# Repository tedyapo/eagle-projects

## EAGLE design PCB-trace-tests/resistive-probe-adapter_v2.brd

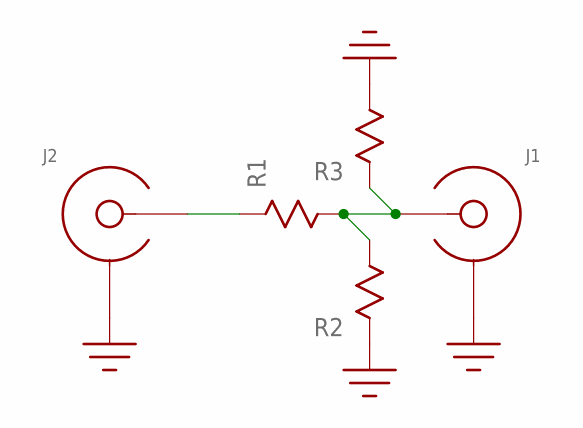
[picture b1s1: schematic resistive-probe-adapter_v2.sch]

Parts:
J1, J2: SMA-EDGE-LAUNCH4020_TAPER; SMA_EDGE_LAUNCH_2L_4020_TAPER
R1, R2, R3: R0603

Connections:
GND: J1.BOTTOM_GND (SHIELD), J1.GND@1 (SHIELD), J1.GND@2 (SHIELD), J1.GND@3 (SHIELD), J1.GND@4 (SHIELD), J1.GND@5 (SHIELD), J1.GND@6 (SHIELD), J1.GND@7 (SHIELD), J1.GND@8 (SHIELD), J1.GND@14 (SHIELD), J1.GND@15 (SHIELD), J1.GND@16 (SHIELD), J1.GND@17 (SHIELD), J1.GND_PAD1 (SHIELD), J1.GND_PAD2 (SHIELD), J1.P$1 (SHIELD), J1.P$2 (SHIELD), J2.BOTTOM_GND (SHIELD), J2.GND@1 (SHIELD), J2.GND@2 (SHIELD), J2.GND@3 (SHIELD), J2.GND@4 (SHIELD), J2.GND@5 (SHIELD), J2.GND@6 (SHIELD), J2.GND@7 (SHIELD), J2.GND@8 (SHIELD), J2.GND@14 (SHIELD), J2.GND@15 (SHIELD), J2.GND@16 (SHIELD), J2.GND@17 (SHIELD), J2.GND_PAD1 (SHIELD), J2.GND_PAD2 (SHIELD), J2.P$1 (SHIELD), J2.P$2 (SHIELD), R2.P$1, R3.P$2
unnamed: J2.CENTER@1 (CENTER), R1.P$1
unnamed: J1.CENTER@1 (CENTER), R1.P$2, R2.P$2, R3.P$1

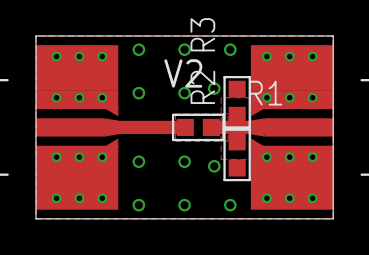
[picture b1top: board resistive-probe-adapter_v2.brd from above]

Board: 2 copper layers, 16.5 x 10.2 mm, 5 parts (0 on the bottom side), 3 nets.

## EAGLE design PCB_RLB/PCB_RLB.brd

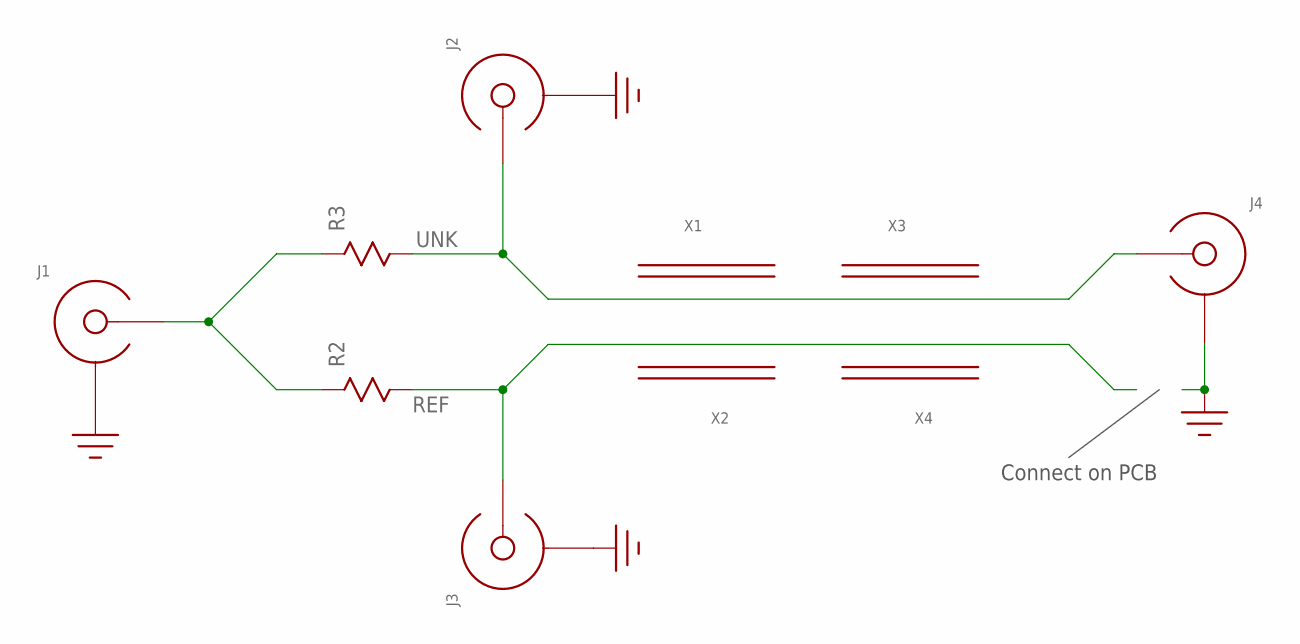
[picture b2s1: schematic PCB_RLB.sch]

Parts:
J1, J2, J3, J4: EDGE_LAUNCH_JACK; EDGE_LAUNCH_RF_CON
R2, R3: R0603
X1, X2, X3, X4: FERRITE_PLATE; FERRITE-MP0350

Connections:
GND: J1.GND@1 (SHIELD), J1.GND@2 (SHIELD), J1.GND@3 (SHIELD), J1.GND@4 (SHIELD), J1.GND@5 (SHIELD), J1.GND@6 (SHIELD), J1.GND@7 (SHIELD), J1.GND@8 (SHIELD), J1.GND@9 (SHIELD), J1.GND@10 (SHIELD), J1.GND@11 (SHIELD), J1.GND@12 (SHIELD), J1.SHIELD@1 (SHIELD), J1.SHIELD@2 (SHIELD), J2.GND@1 (SHIELD), J2.GND@2 (SHIELD), J2.GND@3 (SHIELD), J2.GND@4 (SHIELD), J2.GND@5 (SHIELD), J2.GND@6 (SHIELD), J2.GND@7 (SHIELD), J2.GND@8 (SHIELD), J2.GND@9 (SHIELD), J2.GND@10 (SHIELD), J2.GND@11 (SHIELD), J2.GND@12 (SHIELD), J2.SHIELD@1 (SHIELD), J2.SHIELD@2 (SHIELD), J3.GND@1 (SHIELD), J3.GND@2 (SHIELD), J3.GND@3 (SHIELD), J3.GND@4 (SHIELD), J3.GND@5 (SHIELD), J3.GND@6 (SHIELD), J3.GND@7 (SHIELD), J3.GND@8 (SHIELD), J3.GND@9 (SHIELD), J3.GND@10 (SHIELD), J3.GND@11 (SHIELD), J3.GND@12 (SHIELD), J3.SHIELD@1 (SHIELD), J3.SHIELD@2 (SHIELD), J4.GND@1 (SHIELD), J4.GND@2 (SHIELD), J4.GND@3 (SHIELD), J4.GND@4 (SHIELD), J4.GND@5 (SHIELD), J4.GND@6 (SHIELD), J4.GND@7 (SHIELD), J4.GND@8 (SHIELD), J4.GND@9 (SHIELD), J4.GND@10 (SHIELD), J4.GND@11 (SHIELD), J4.GND@12 (SHIELD), J4.SHIELD@1 (SHIELD), J4.SHIELD@2 (SHIELD)
unnamed: J1.CENTER, R2.P$1, R3.P$1
REF: J3.CENTER, R2.P$2
UNK: J2.CENTER, J4.CENTER, R3.P$2

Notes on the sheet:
Connect on PCB

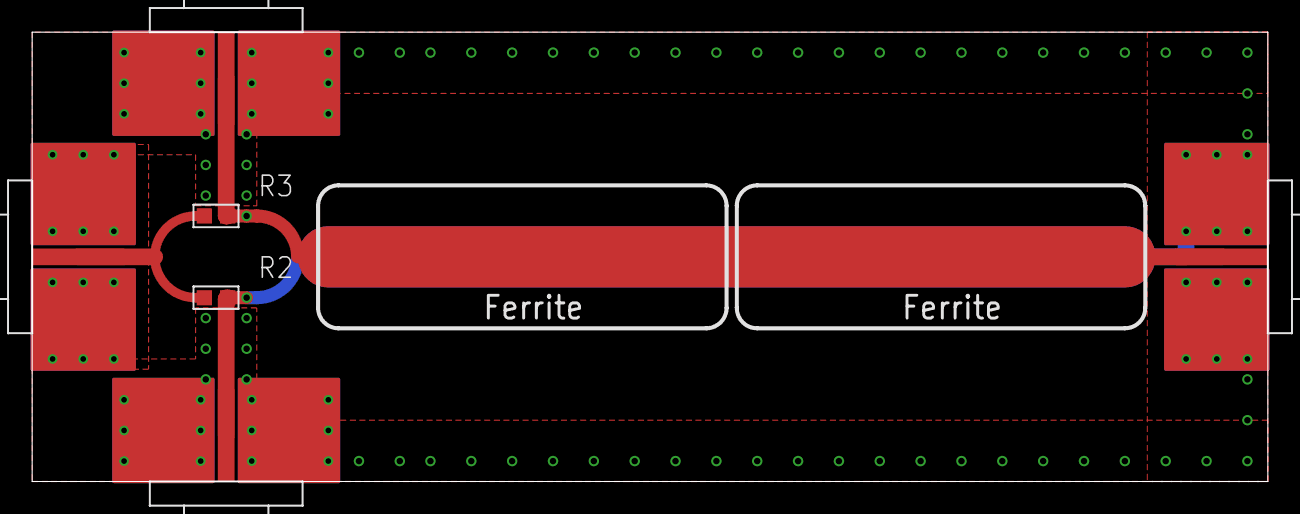
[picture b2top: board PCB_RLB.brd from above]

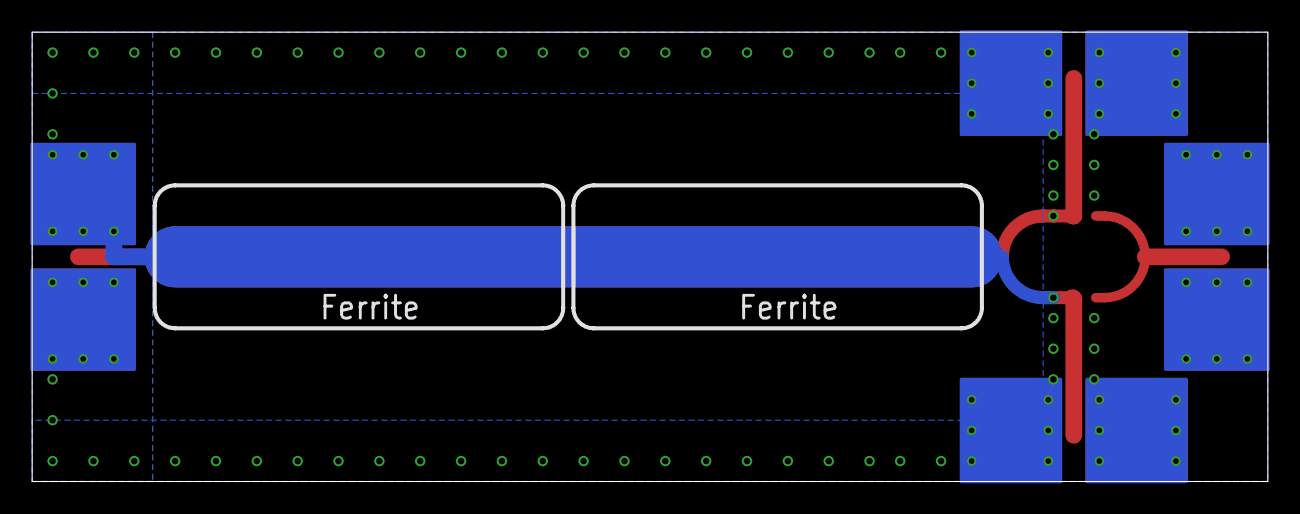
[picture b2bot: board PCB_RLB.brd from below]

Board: 2 copper layers, 76.8 x 27.9 mm, 10 parts (2 on the bottom side), 4 nets.

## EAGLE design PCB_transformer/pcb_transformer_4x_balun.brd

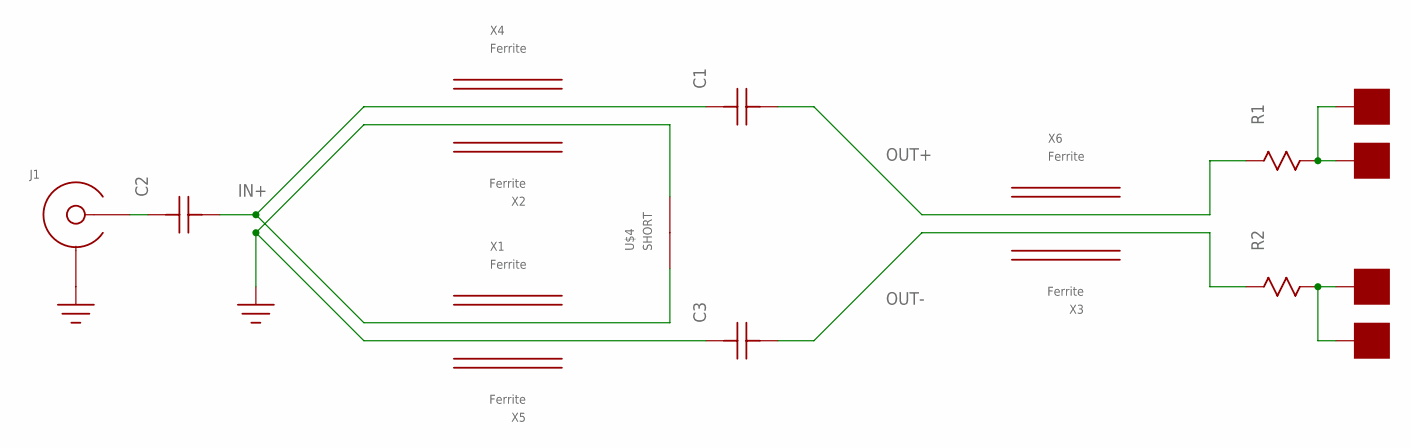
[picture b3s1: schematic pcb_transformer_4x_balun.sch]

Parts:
C1, C2, C3: C0603
J1: EDGE_LAUNCH_JACK; EDGE_LAUNCH_RF_CON
R1, R2: R0603
U$2, U$5, U$6, U$7: PAD50MIL; PAD_50MIL
U$4: SHORT; SHORT_57MIL
X1, X2, X3, X4, X5, X6: Ferrite; FERRITE-MP0350

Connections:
GND: C3.P$2, J1.GND@1 (SHIELD), J1.GND@2 (SHIELD), J1.GND@3 (SHIELD), J1.GND@4 (SHIELD), J1.GND@5 (SHIELD), J1.GND@6 (SHIELD), J1.GND@7 (SHIELD), J1.GND@8 (SHIELD), J1.GND@9 (SHIELD), J1.GND@10 (SHIELD), J1.GND@11 (SHIELD), J1.GND@12 (SHIELD), J1.SHIELD@1 (SHIELD), J1.SHIELD@2 (SHIELD), U$4.P$2
IN+: C1.P$2, C2.P$1, U$4.P$1
unnamed: C2.P$2, J1.CENTER
unnamed: R1.P$2, U$2.P$1, U$6.P$1
unnamed: R2.P$2, U$5.P$1, U$7.P$1
OUT+: C1.P$1, R1.P$1
OUT-: C3.P$1, R2.P$1

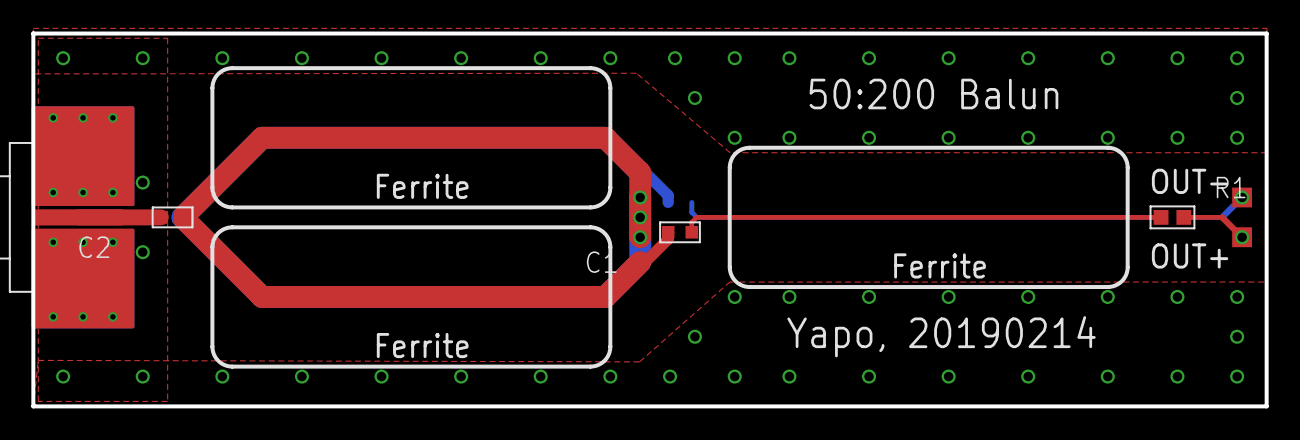
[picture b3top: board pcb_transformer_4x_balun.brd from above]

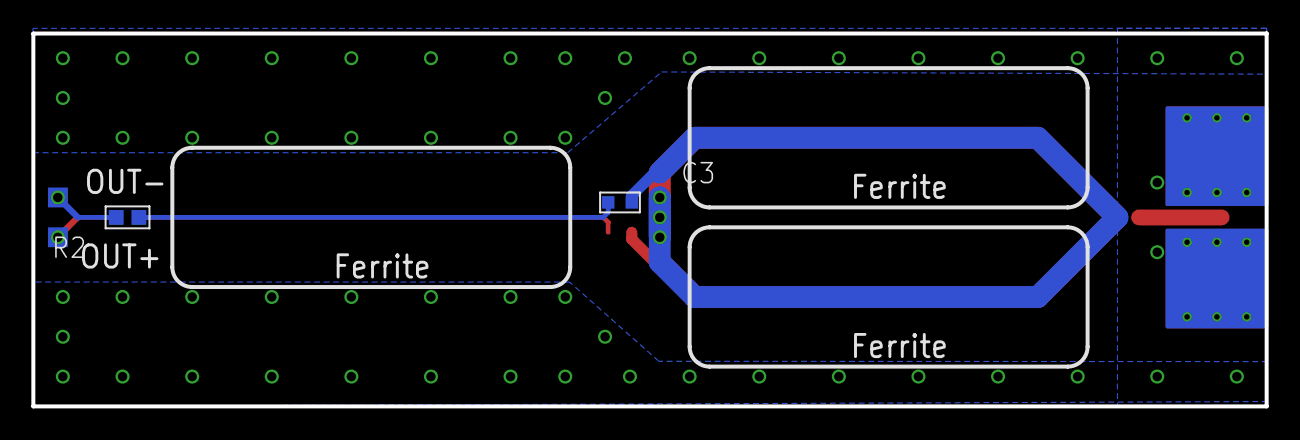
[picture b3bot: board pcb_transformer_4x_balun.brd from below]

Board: 2 copper layers, 78.7 x 23.8 mm, 17 parts (7 on the bottom side), 7 nets.

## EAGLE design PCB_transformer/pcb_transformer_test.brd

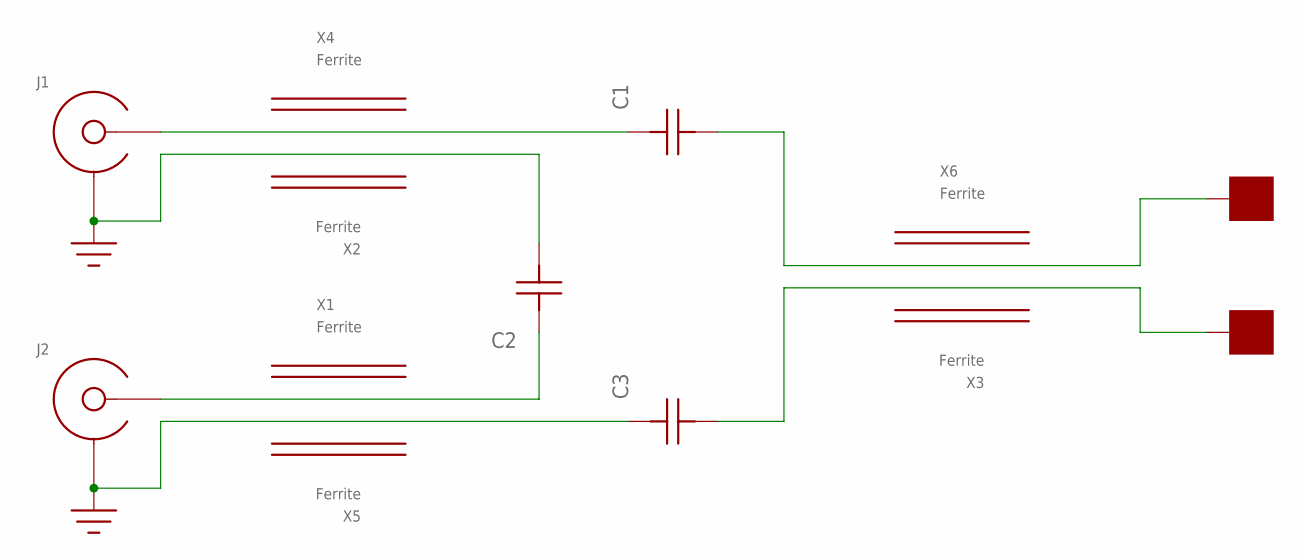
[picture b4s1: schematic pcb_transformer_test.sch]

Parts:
C1, C2, C3: C0603
J1, J2: EDGE_LAUNCH_JACK; EDGE_LAUNCH_RF_CON
U$2, U$5: PAD50MIL; PAD_50MIL
X1, X2, X3, X4, X5, X6: Ferrite; FERRITE-MP0350

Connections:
GND: C2.P$1, C3.P$2, J1.GND@1 (SHIELD), J1.GND@2 (SHIELD), J1.GND@3 (SHIELD), J1.GND@4 (SHIELD), J1.GND@5 (SHIELD), J1.GND@6 (SHIELD), J1.GND@7 (SHIELD), J1.GND@8 (SHIELD), J1.GND@9 (SHIELD), J1.GND@10 (SHIELD), J1.GND@11 (SHIELD), J1.GND@12 (SHIELD), J1.SHIELD@1 (SHIELD), J1.SHIELD@2 (SHIELD), J2.GND@1 (SHIELD), J2.GND@2 (SHIELD), J2.GND@3 (SHIELD), J2.GND@4 (SHIELD), J2.GND@5 (SHIELD), J2.GND@6 (SHIELD), J2.GND@7 (SHIELD), J2.GND@8 (SHIELD), J2.GND@9 (SHIELD), J2.GND@10 (SHIELD), J2.GND@11 (SHIELD), J2.GND@12 (SHIELD), J2.SHIELD@1 (SHIELD), J2.SHIELD@2 (SHIELD)
unnamed: C1.P$2, J1.CENTER
unnamed: C2.P$2, J2.CENTER
unnamed: C1.P$1, U$2.P$1
unnamed: C3.P$1, U$5.P$1

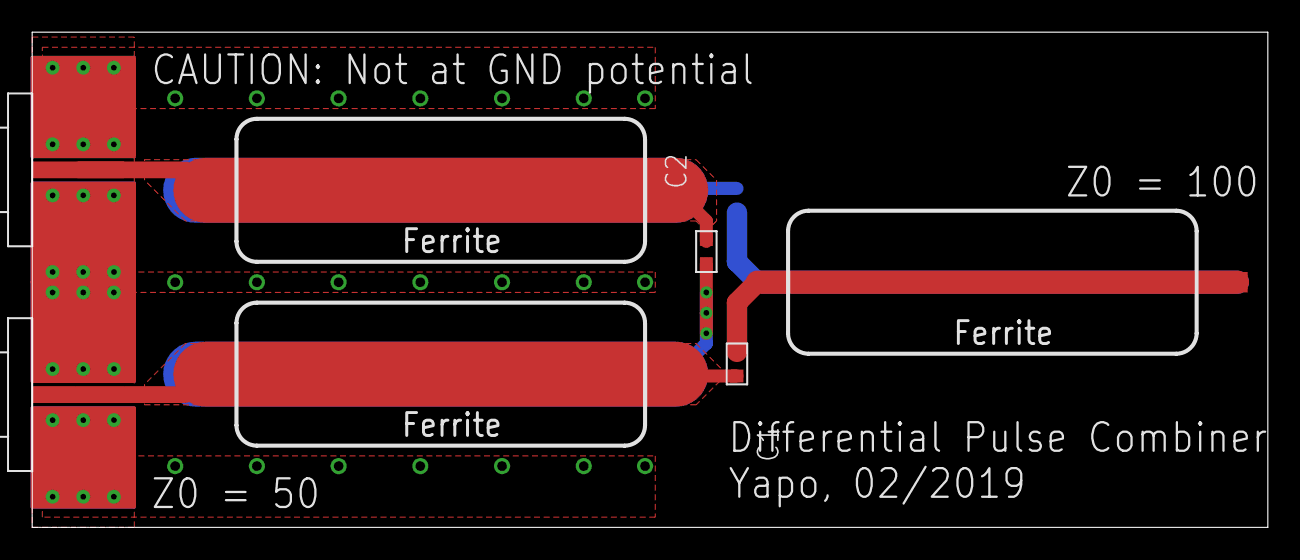
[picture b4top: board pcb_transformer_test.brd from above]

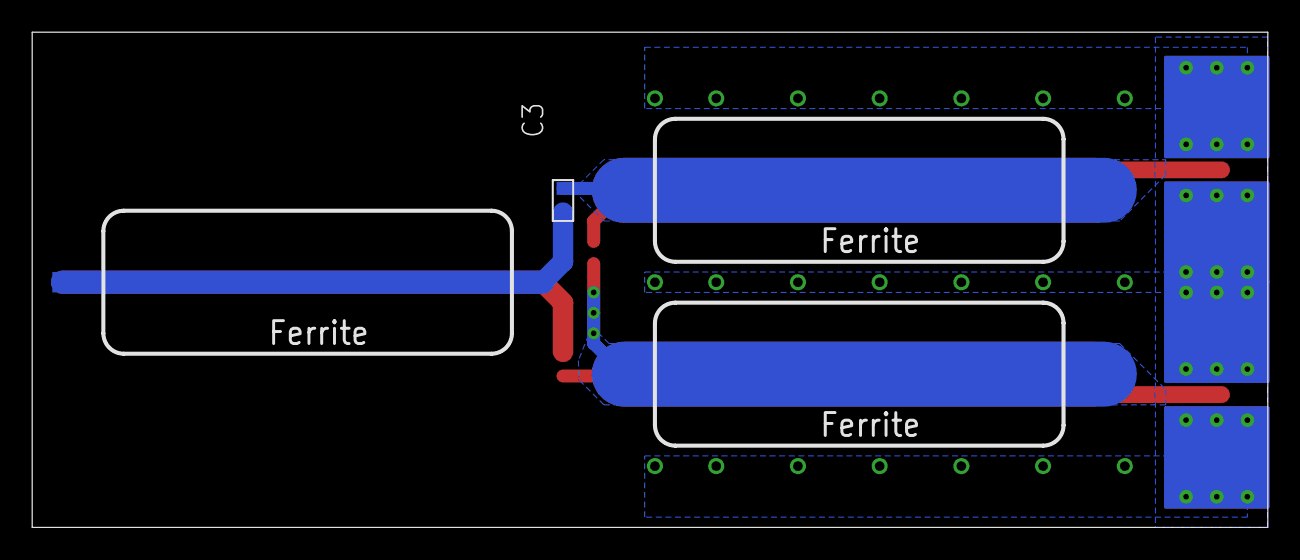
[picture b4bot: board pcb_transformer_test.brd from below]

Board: 2 copper layers, 76.8 x 30.8 mm, 13 parts (5 on the bottom side), 5 nets.

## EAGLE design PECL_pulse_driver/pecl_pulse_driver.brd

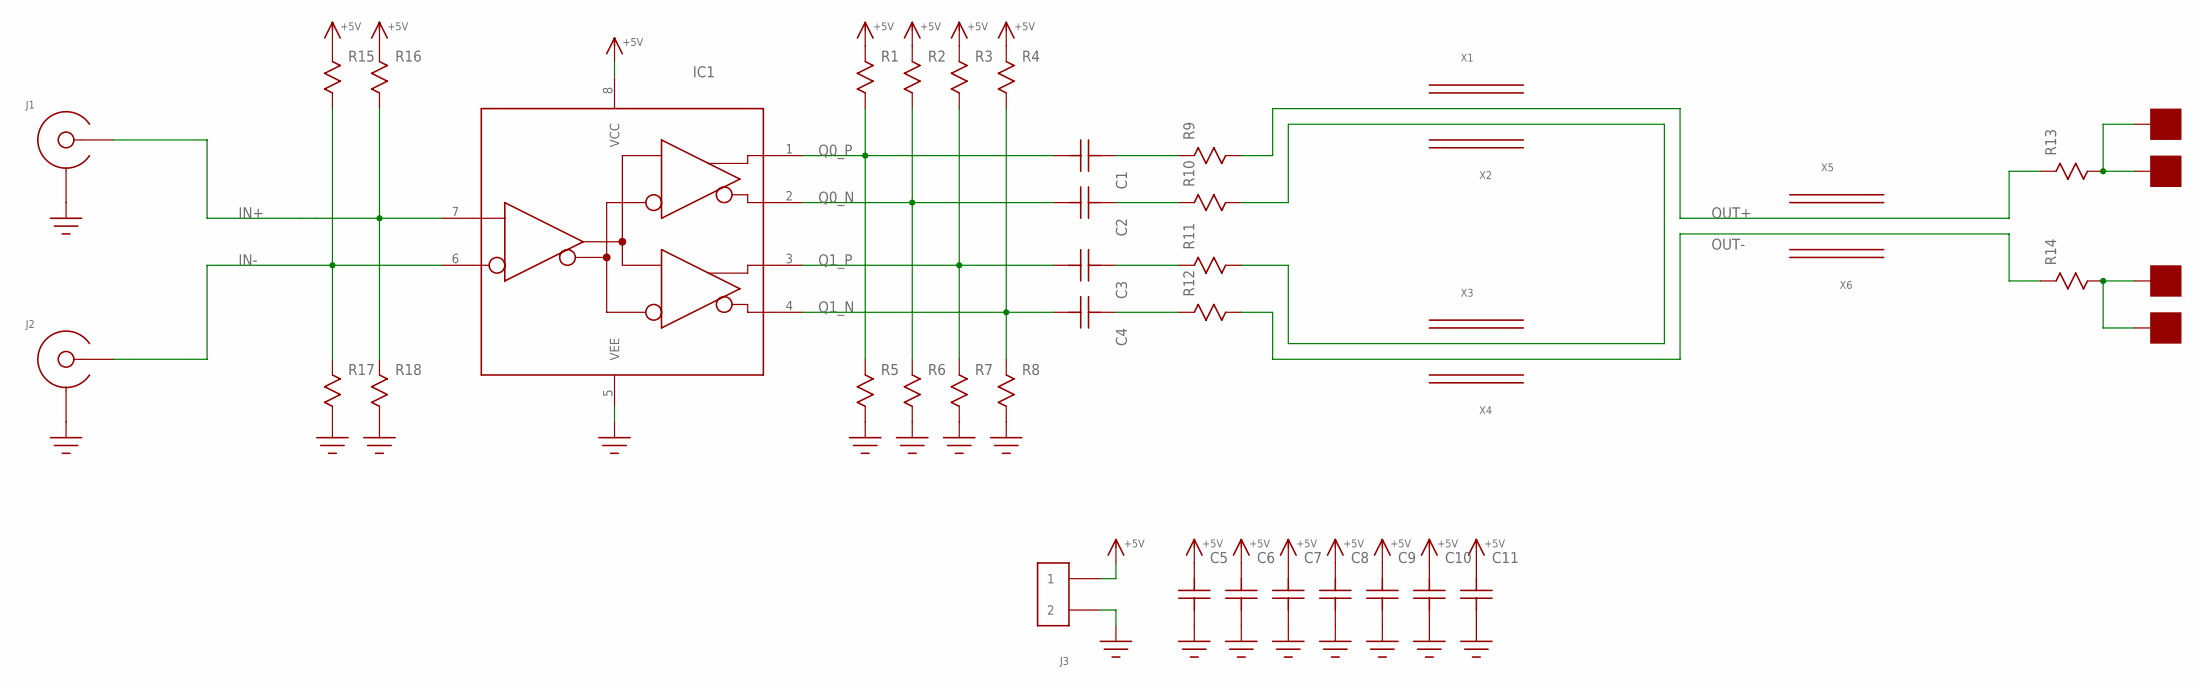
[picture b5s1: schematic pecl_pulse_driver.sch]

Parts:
C1, C2, C3, C4, C5, C6, C8, C9, C10, C11: C0603
C7: C0805; 0805
IC1: SY10EP89V; SOIC8
J1, J2: EDGE_LAUNCH_JACK; EDGE_LAUNCH_RF_CON
J3: HEADER_2PIN
R1, R2, R3, R4, R5, R6, R7, R8, R9, R10, R11, R12, R13, R14, R15, R16, R17, R18: R0603
U$4, U$5, U$35, U$36: PAD50MIL; PAD_50MIL
X1, X2, X3, X4, X5, X6: FERRITE_PLATE; FERRITE-MP0350

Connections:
+5V: C5.P$2, C6.P$2, C7.P$2, C8.P$2, C9.P$2, C10.P$2, C11.P$2, IC1.8 (VCC), J3.1, R1.P$1, R2.P$1, R3.P$1, R4.P$1, R15.P$1, R16.P$1
GND: C5.P$1, C6.P$1, C7.P$1, C8.P$1, C9.P$1, C10.P$1, C11.P$1, IC1.5 (VEE), J1.GND@1 (SHIELD), J1.GND@2 (SHIELD), J1.GND@3 (SHIELD), J1.GND@4 (SHIELD), J1.GND@5 (SHIELD), J1.GND@6 (SHIELD), J1.GND@7 (SHIELD), J1.GND@8 (SHIELD), J1.GND@9 (SHIELD), J1.GND@10 (SHIELD), J1.GND@11 (SHIELD), J1.GND@12 (SHIELD), J1.SHIELD@1 (SHIELD), J1.SHIELD@2 (SHIELD), J2.GND@1 (SHIELD), J2.GND@2 (SHIELD), J2.GND@3 (SHIELD), J2.GND@4 (SHIELD), J2.GND@5 (SHIELD), J2.GND@6 (SHIELD), J2.GND@7 (SHIELD), J2.GND@8 (SHIELD), J2.GND@9 (SHIELD), J2.GND@10 (SHIELD), J2.GND@11 (SHIELD), J2.GND@12 (SHIELD), J2.SHIELD@1 (SHIELD), J2.SHIELD@2 (SHIELD), J3.2, R5.P$2, R6.P$2, R7.P$2, R8.P$2, R17.P$2, R18.P$2
IN+: IC1.7 (D), J1.CENTER, R16.P$2, R18.P$1
IN-: IC1.6 (!D!), J2.CENTER, R15.P$2, R17.P$1
unnamed: C1.P$2, R9.P$1
unnamed: C2.P$2, R10.P$1
unnamed: C3.P$2, R11.P$1
unnamed: C4.P$2, R12.P$1
unnamed: R10.P$2, R11.P$2
unnamed: R13.P$2, U$4.P$1, U$35.P$1
unnamed: R14.P$2, U$5.P$1, U$36.P$1
OUT+: R9.P$2, R13.P$1
OUT-: R12.P$2, R14.P$1
Q0_N: C2.P$1, IC1.2 (!Q0!), R2.P$2, R6.P$1
Q0_P: C1.P$1, IC1.1 (Q0), R1.P$2, R5.P$1
Q1_N: C4.P$1, IC1.4 (!Q1!), R4.P$2, R8.P$1
Q1_P: C3.P$1, IC1.3 (Q1), R3.P$2, R7.P$1

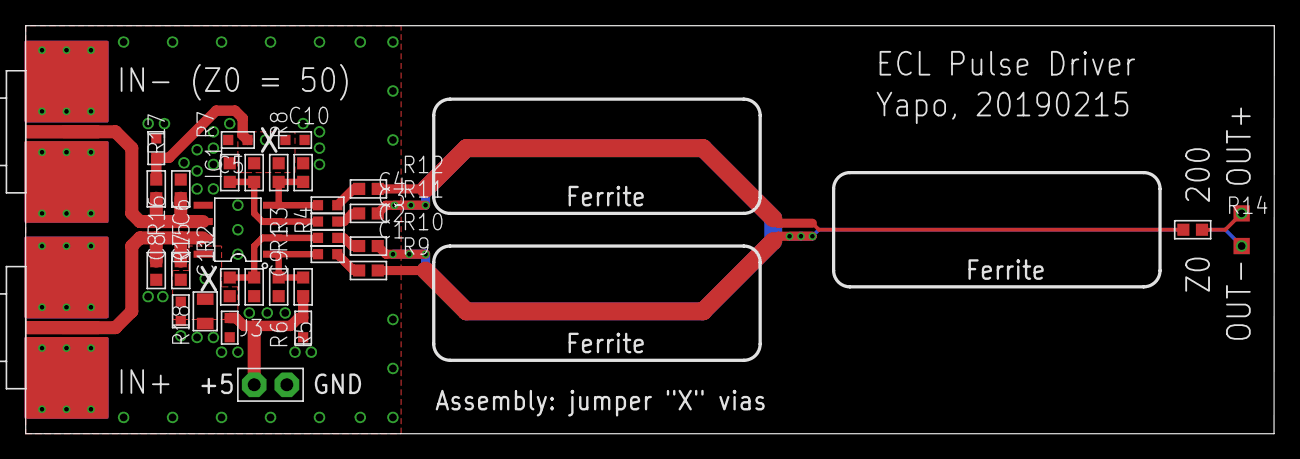
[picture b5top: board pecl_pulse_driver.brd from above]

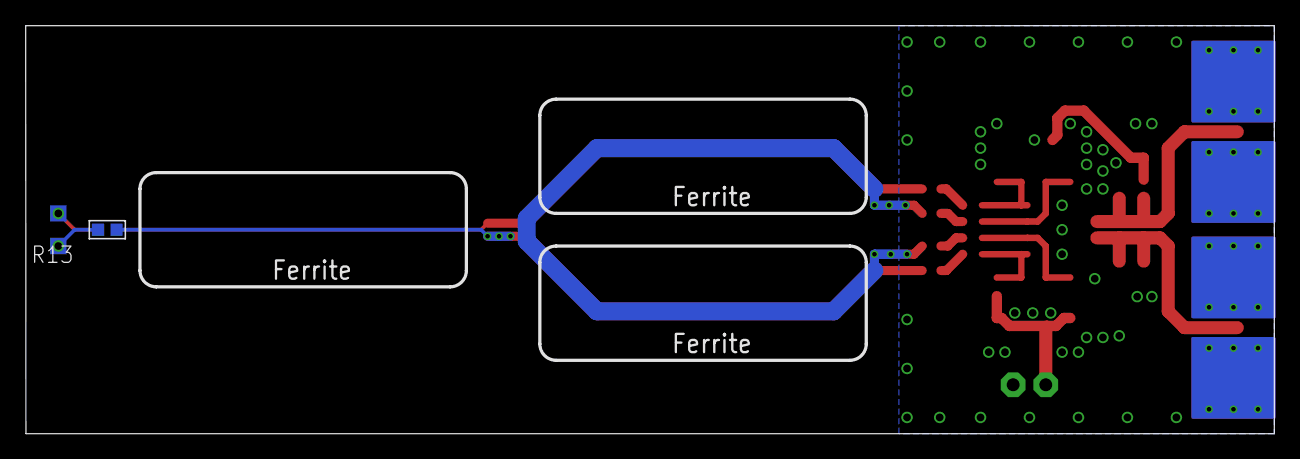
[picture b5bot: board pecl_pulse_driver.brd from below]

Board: 2 copper layers, 97.2 x 31.8 mm, 43 parts (6 on the bottom side), 17 nets.

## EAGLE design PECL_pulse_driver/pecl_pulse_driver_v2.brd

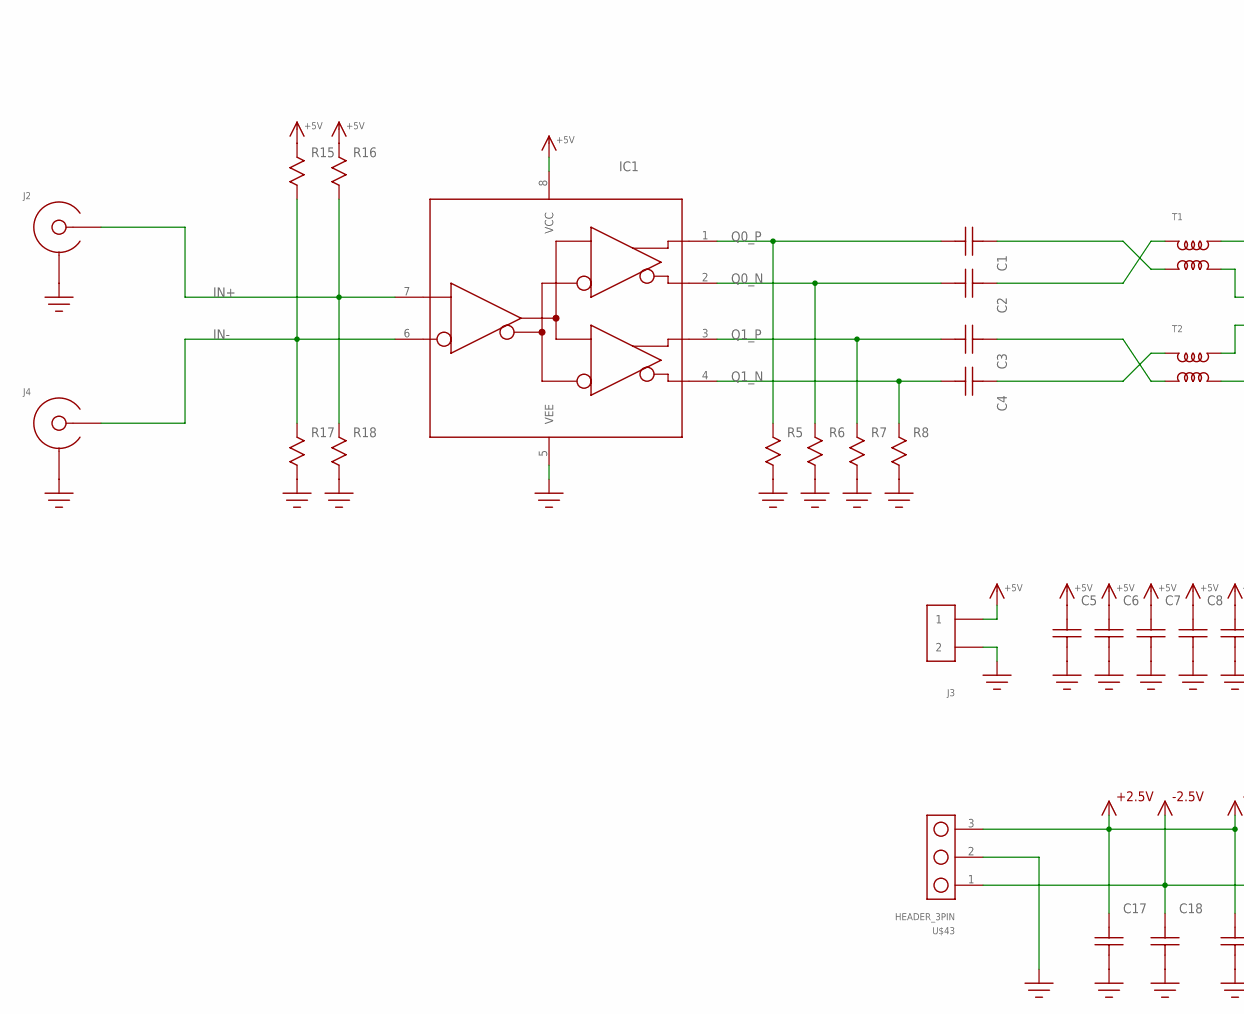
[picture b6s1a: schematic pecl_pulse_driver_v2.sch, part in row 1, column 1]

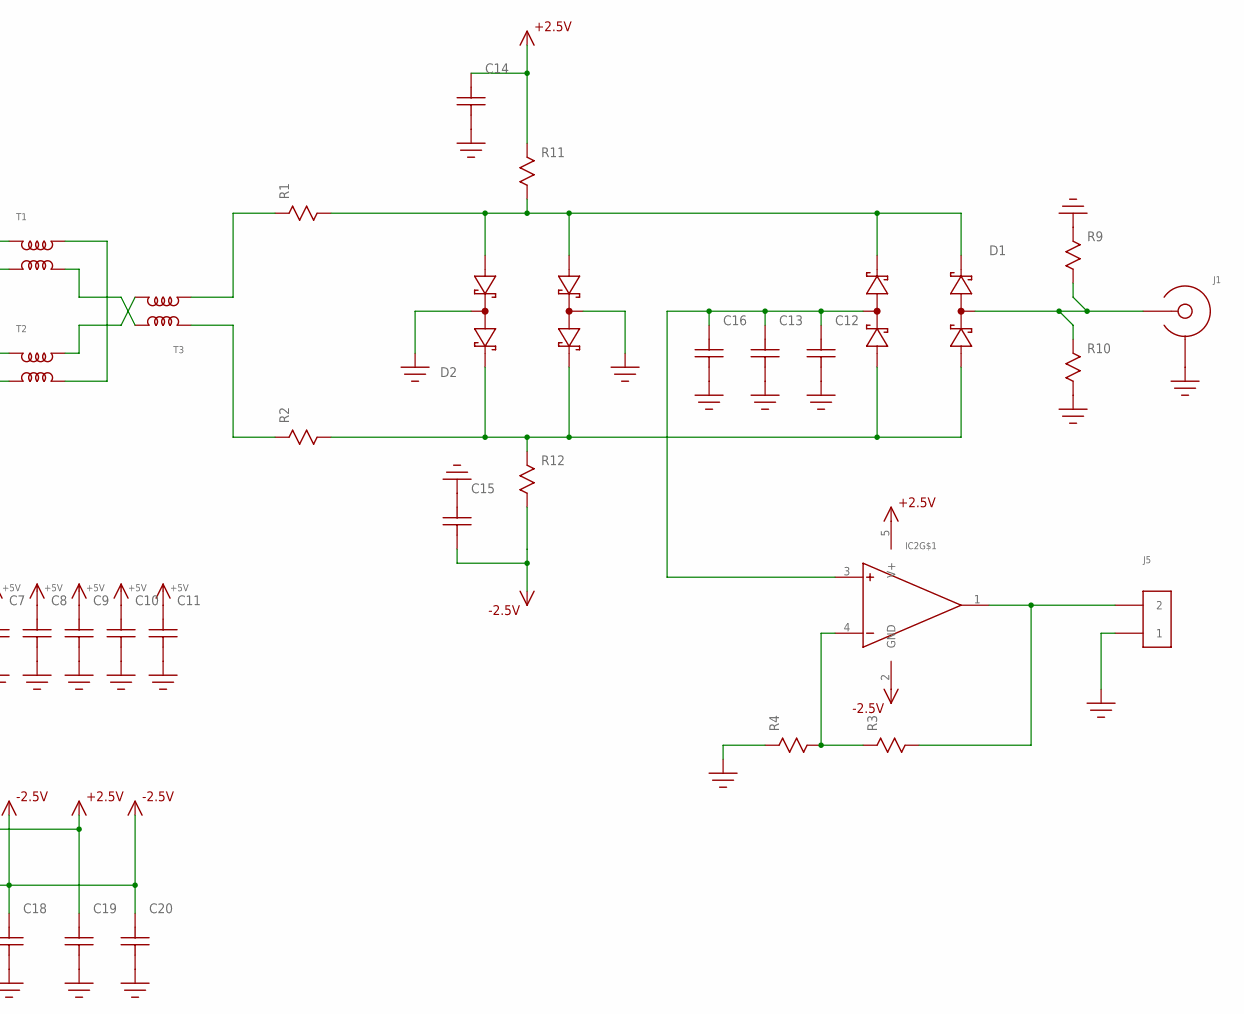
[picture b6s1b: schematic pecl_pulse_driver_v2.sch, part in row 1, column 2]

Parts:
C1, C2, C3, C4, C12, C13, C14, C15, C16: C; C0402
C5, C6, C8, C9, C10, C11, C17, C18, C19, C20: C0603
C7: C0805; 0805
D1, D2: SMS3923-081; SC-88
IC1: SY10EP89V; SOIC8
IC2: MCP6V81; SOT23-5
J1, J2, J4: SMA-EDGE-LAUNCH4L-4020-TAPER-FIXED; SMA_EDGE_LAUNCH_4L_4020_TAPER_FIXED
J3, J5: HEADER_2PIN
R1, R2, R9, R10, R11, R12: R0402; 0402
R3, R4, R5, R6, R7, R8, R15, R16, R17, R18: R0603
T1, T2, T3: MABA007159; MABAES0061
U$43: HEADER_3PIN

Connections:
+2.5V: C14.2, C17.P$2, C19.P$2, IC2.5 (V+), R11.1, U$43.3
+5V: C5.P$2, C6.P$2, C7.P$2, C8.P$2, C9.P$2, C10.P$2, C11.P$2, IC1.8 (VCC), J3.1, R15.P$1, R16.P$1
-2.5V: C15.1, C18.P$2, C20.P$2, IC2.2 (GND), R12.2, U$43.1
GND: C5.P$1, C6.P$1, C7.P$1, C8.P$1, C9.P$1, C10.P$1, C11.P$1, C12.1, C13.1, C14.1, C15.2, C16.1, C17.P$1, C18.P$1, C19.P$1, C20.P$1, D2.2 (COMMON0), D2.5 (COMMON1), IC1.5 (VEE), J1.BOTTOM_GND (SHIELD), J1.GND@1 (SHIELD), J1.GND@2 (SHIELD), J1.GND@3 (SHIELD), J1.GND@4 (SHIELD), J1.GND@5 (SHIELD), J1.GND@6 (SHIELD), J1.GND@7 (SHIELD), J1.GND@8 (SHIELD), J1.GND@14 (SHIELD), J1.GND@15 (SHIELD), J1.GND@16 (SHIELD), J1.GND@17 (SHIELD), J1.GND_PAD1 (SHIELD), J1.GND_PAD2 (SHIELD), J1.P$1 (SHIELD), J1.P$2 (SHIELD), J2.BOTTOM_GND (SHIELD), J2.GND@1 (SHIELD), J2.GND@2 (SHIELD), J2.GND@3 (SHIELD), J2.GND@4 (SHIELD), J2.GND@5 (SHIELD), J2.GND@6 (SHIELD), J2.GND@7 (SHIELD), J2.GND@8 (SHIELD), J2.GND@14 (SHIELD), J2.GND@15 (SHIELD), J2.GND@16 (SHIELD), J2.GND@17 (SHIELD), J2.GND_PAD1 (SHIELD), J2.GND_PAD2 (SHIELD), J2.P$1 (SHIELD), J2.P$2 (SHIELD), J3.2, J4.BOTTOM_GND (SHIELD), J4.GND@1 (SHIELD), J4.GND@2 (SHIELD), J4.GND@3 (SHIELD), J4.GND@4 (SHIELD), J4.GND@5 (SHIELD), J4.GND@6 (SHIELD), J4.GND@7 (SHIELD), J4.GND@8 (SHIELD), J4.GND@14 (SHIELD), J4.GND@15 (SHIELD), J4.GND@16 (SHIELD), J4.GND@17 (SHIELD), J4.GND_PAD1 (SHIELD), J4.GND_PAD2 (SHIELD), J4.P$1 (SHIELD), J4.P$2 (SHIELD), J5.1, R4.P$1, R5.P$2, R6.P$2, R7.P$2, R8.P$2, R9.1, R10.2, R17.P$2, R18.P$2, U$43.2
IN+: IC1.7 (D), J2.CENTER@1 (CENTER), J2.P$3 (CENTER), R16.P$2, R18.P$1
IN-: IC1.6 (!D!), J4.CENTER@1 (CENTER), J4.P$3 (CENTER), R15.P$2, R17.P$1
unnamed: C4.2, T2.5
unnamed: C12.2, C13.2, C16.2, D1.5 (COMMON1), IC2.3 (+)
unnamed: T1.1, T2.3
unnamed: D1.2 (COMMON0), J1.CENTER@1 (CENTER), J1.P$3 (CENTER), R9.2, R10.1
unnamed: T1.3, T3.1
unnamed: T2.1, T3.3
unnamed: D1.3 (CATHODE0), D1.4 (CATHODE1), D2.1 (ANODE0), D2.6 (ANODE1), R1.2, R11.2
unnamed: C2.2, T1.5
unnamed: C3.2, T2.4
unnamed: D1.1 (ANODE0), D1.6 (ANODE1), D2.3 (CATHODE0), D2.4 (CATHODE1), R2.2, R12.1
unnamed: R1.1, T3.4
unnamed: R2.1, T3.5
unnamed: IC2.4 (-), R3.P$1, R4.P$2
unnamed: C1.2, T1.4
unnamed: IC2.1 (OUT), J5.2, R3.P$2
Q0_N: C2.1, IC1.2 (!Q0!), R6.P$1
Q0_P: C1.1, IC1.1 (Q0), R5.P$1
Q1_N: C4.1, IC1.4 (!Q1!), R8.P$1
Q1_P: C3.1, IC1.3 (Q1), R7.P$1

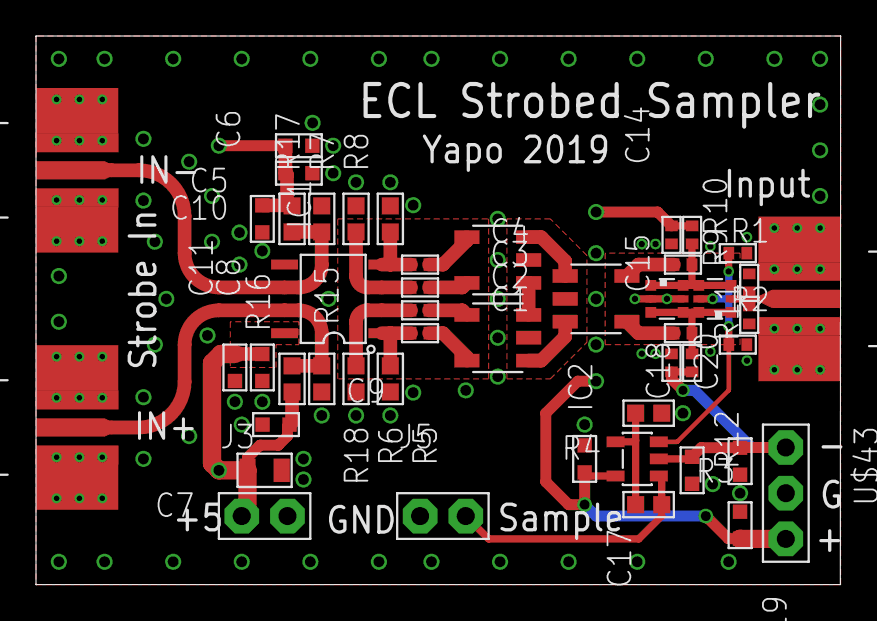
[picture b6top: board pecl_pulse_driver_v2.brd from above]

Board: 2 copper layers, 44.7 x 30.5 mm, 49 parts (1 on the bottom side), 25 nets.
